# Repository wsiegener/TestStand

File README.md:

# Model Rocket Thrust Measurement Test Stand
* An RIT SPEX solo project developed by Billy Siegener

### Current Functionality
* Records and displays measurements from a 50kg load cell via an [HX711](https://cdn.sparkfun.com/datasheets/Sensors/ForceFlex/hx711_english.pdf "Amplifier datasheet") load cell amplifier module.
  * [HX711 Library](https://github.com/bogde/HX711 "HX711Library")
* Automatic scale factor tuning
* Improved tare functionality for dealing with noisy circuitry
* 1602A LCD implemenation

### Future Functionality
* ...

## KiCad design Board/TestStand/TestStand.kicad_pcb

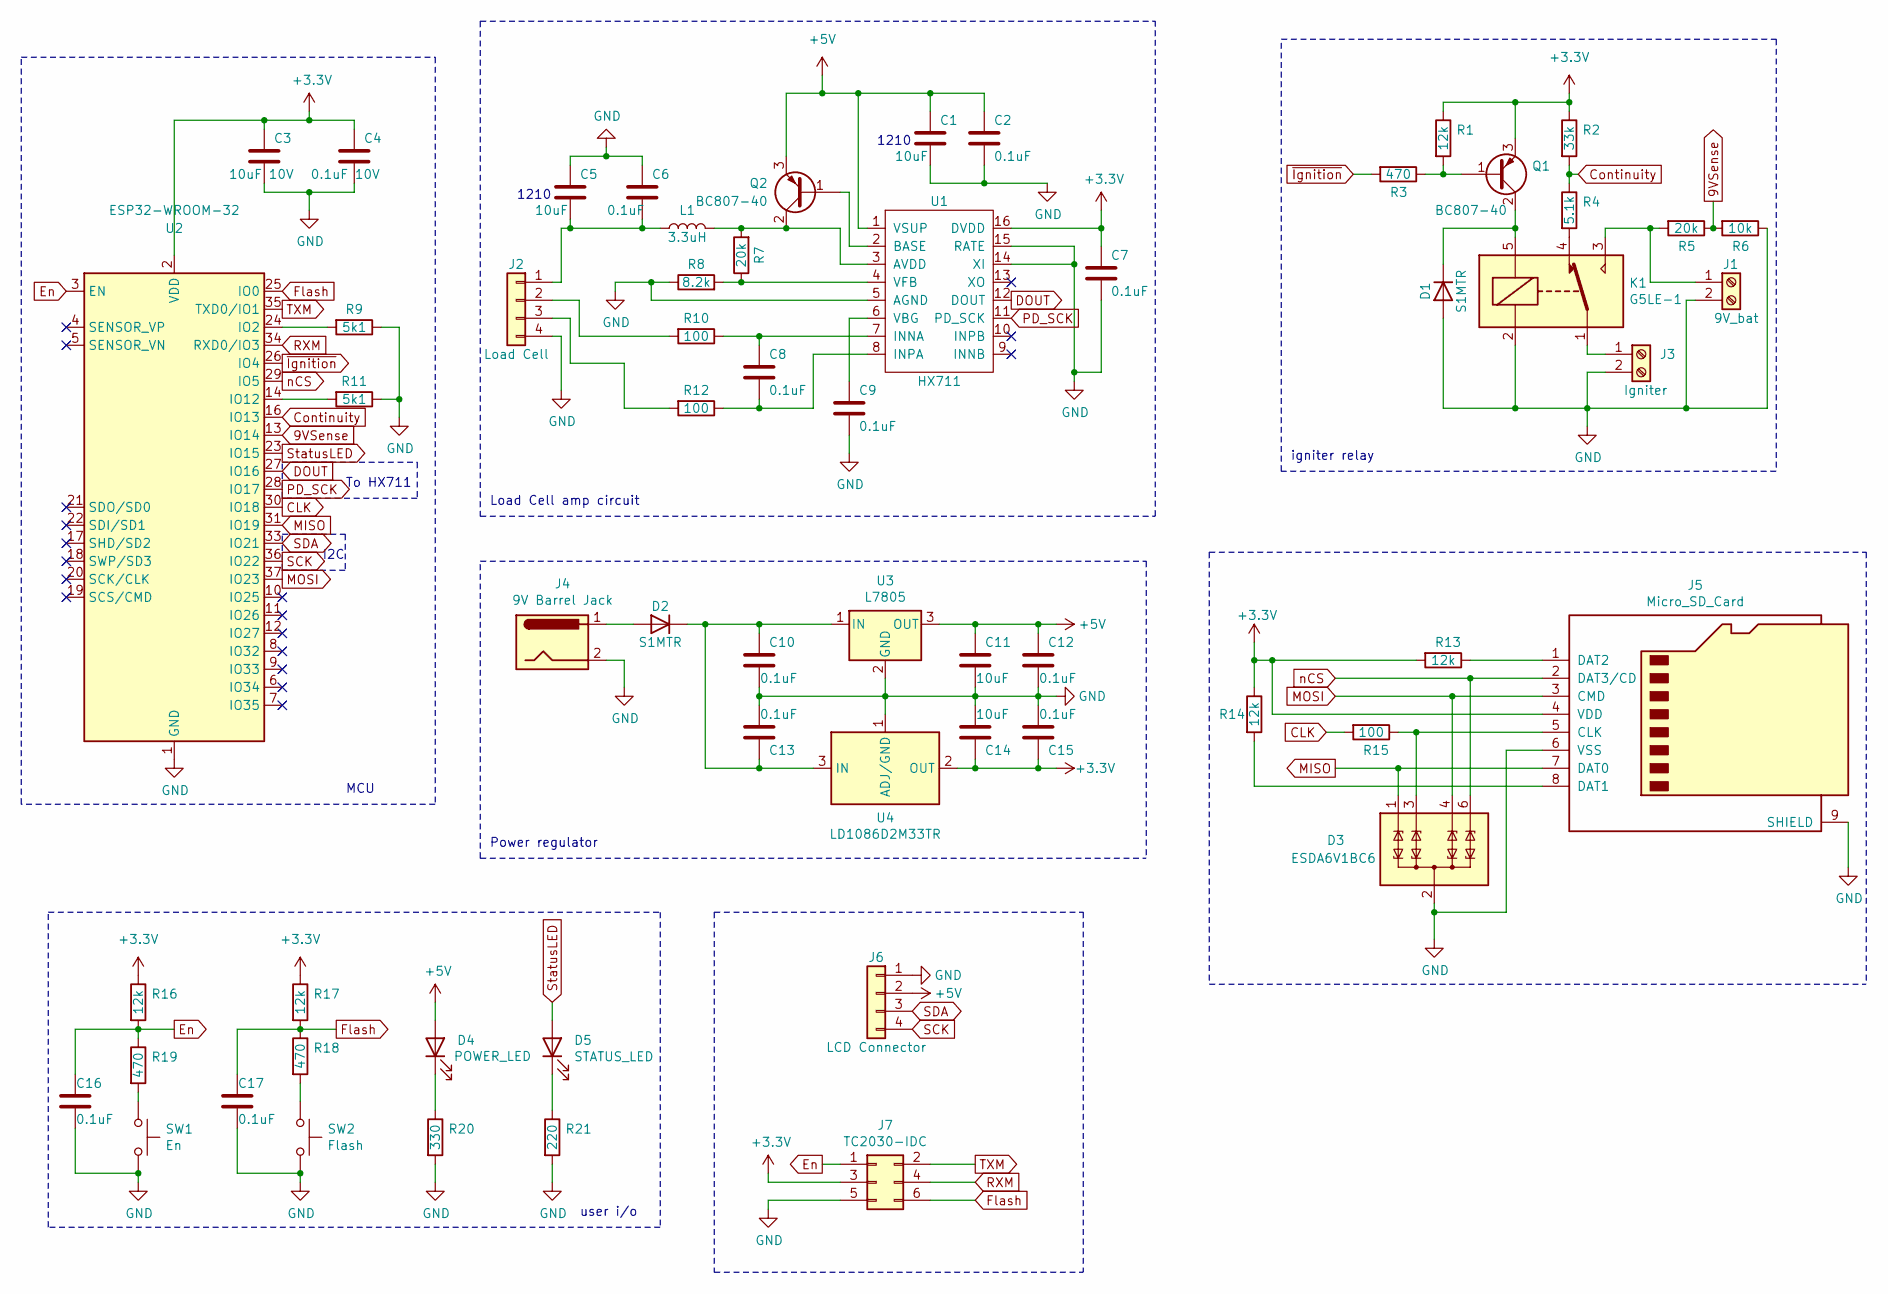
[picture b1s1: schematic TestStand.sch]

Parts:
C1, C5: 10uF; C_1210_3225Metric_Pad1.42x2.65mm_HandSolder
C2, C6, C7, C8, C9, C10, C12, C13, C15, C16, C17: 0.1uF; C_0805_2012Metric_Pad1.15x1.40mm_HandSolder
C3: 10uF 10V; C_0805_2012Metric_Pad1.15x1.40mm_HandSolder
C4: 0.1uF 10V; C_0805_2012Metric_Pad1.15x1.40mm_HandSolder
C11, C14: 10uF; C_0805_2012Metric_Pad1.15x1.40mm_HandSolder
D1, D2: S1MTR; D_SMA_Handsoldering
D3: ESDA6V1BC6; SOT-23-6
D4: POWER_LED; LED_Rectangular_W5.0mm_H2.0mm
D5: STATUS_LED; LED_Rectangular_W5.0mm_H2.0mm
J1: 9V_bat; TerminalBlock_Phoenix_PT-1,5-2-5.0-H_1x02_P5.00mm_Horizontal
J2: Load Cell; Molex_Micro-Fit_3.0_43045-0400_2x02_P3.00mm_Horizontal
J3: Igniter; TerminalBlock_Phoenix_PT-1,5-2-5.0-H_1x02_P5.00mm_Horizontal
J4: 9V Barrel Jack; BarrelJack_CUI_PJ-036AH-SMT_Horizontal
J5: Micro_SD_Card; microSD_HC_Molex_104031-0811
J6: LCD Connector; PinHeader_1x04_P2.54mm_Vertical
J7: TC2030-IDC; Tag-Connect_TC2030-IDC-FP_2x03_P1.27mm_Vertical
K1: G5LE-1; Relay_SPDT_Omron-G5LE-1
L1: 3.3uH; L_0805_2012Metric_Pad1.15x1.40mm_HandSolder
Q1, Q2: BC807-40; SOT-23_Handsoldering
R1, R13, R14, R16, R17: 12k; R_0805_2012Metric_Pad1.15x1.40mm_HandSolder
R2: 33k; R_0805_2012Metric_Pad1.15x1.40mm_HandSolder
R3, R18, R19: 470; R_0805_2012Metric_Pad1.15x1.40mm_HandSolder
R4: 5.1k; R_0805_2012Metric_Pad1.15x1.40mm_HandSolder
R5, R7: 20k; R_0805_2012Metric_Pad1.15x1.40mm_HandSolder
R6: 10k; R_0805_2012Metric_Pad1.15x1.40mm_HandSolder
R8: 8.2k; R_0805_2012Metric_Pad1.15x1.40mm_HandSolder
R9, R11: 5k1; R_0805_2012Metric_Pad1.15x1.40mm_HandSolder
R10, R12, R15: 100; R_0805_2012Metric_Pad1.15x1.40mm_HandSolder
R20: 330; R_0805_2012Metric_Pad1.15x1.40mm_HandSolder
R21: 220; R_0805_2012Metric_Pad1.15x1.40mm_HandSolder
SW1: En; SW_Push_1P1T_NO_6x6mm_H9.5mm
SW2: Flash; SW_Push_1P1T_NO_6x6mm_H9.5mm
U1: HX711; STC_SOP-16_3.9x9.9mm_P1.27mm
U2: ESP32-WROOM-32; ESP32-WROOM-32U
U3: L7805; TO-263-2
U4: LD1086D2M33TR; TO-263-3_TabPin2

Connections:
9VSense: R5.1, R6.2, U2.13 (IO14)
+3V3: C3.1, C4.1, C7.1, C14.2, C15.2, J5.4 (VDD), J7.3, Q1.3 (E), R1.1, R2.1, R13.2, R14.1, R16.1, R17.1, U1.16 (DVDD), U2.2 (VDD), U4.2 (OUT)
+5V: C1.1, C2.1, C11.1, C12.1, D4.2 (A), J6.2, Q2.3 (E), U1.1 (VSUP), U3.3 (OUT)
CLK: R15.2, U2.30 (IO18)
Continuity: R2.2, R4.1, U2.16 (IO13)
DOUT: U1.12 (DOUT), U2.27 (IO16)
En: C16.1, J7.1, R16.2, R19.1, U2.3 (EN)
Flash: C17.1, J7.6, R17.2, R18.1, U2.25 (IO0)
GND: C1.2, C2.2, C3.2, C4.2, C5.1, C6.1, C7.2, C9.2, C10.2, C11.2, C12.2, C13.1, C14.1, C15.1, C16.2, C17.2, D1.2 (A), D3.2 (COM), D3.5 (COM), J1.2, J2.4, J3.2, J4.2, J5.6 (VSS), J5.9 (SHIELD), J6.1, J7.5, K1.2, R6.1, R8.1, R9.1, R11.1, R20.2, R21.2, SW1.2, SW2.2, U1.5 (AGND), U1.14 (XI), U1.15 (RATE), U2.1 (GND), U2.15 (GND), U2.38 (GND), U2.39 (GND), U3.2 (GND), U4.1 (ADJ/GND)
Ignition: R3.2, U2.26 (IO4)
MISO: D3.1 (TVS1), J5.7 (DAT0), U2.31 (IO19)
MOSI: D3.4 (TVS3), J5.3 (CMD), U2.37 (IO23)
unnamed: C5.2, C6.2, J2.1, L1.1
unnamed: C8.1, R10.1, U1.7 (INNA)
unnamed: C8.2, R12.1, U1.8 (INPA)
unnamed: C9.1, U1.6 (VBG)
unnamed: C10.1, C13.2, D2.1 (K), U3.1 (IN), U4.3 (IN)
unnamed: D1.1 (K), K1.5, Q1.2 (C)
unnamed: D2.2 (A), J4.1
unnamed: D3.3 (TVS2), J5.5 (CLK), R15.1
unnamed: D4.1 (K), R20.1
unnamed: D5.1 (K), R21.1
unnamed: J1.1, K1.3, R5.2
unnamed: J2.2, R10.2
unnamed: J2.3, R12.2
unnamed: J3.1, K1.1
unnamed: J5.1 (DAT2), R13.1
unnamed: J5.8 (DAT1), R14.2
unnamed: K1.4, R4.2
unnamed: L1.2, Q2.2 (C), R7.2, U1.3 (AVDD)
unnamed: Q1.1 (B), R1.2, R3.1
unnamed: Q2.1 (B), U1.2 (BASE)
unnamed: R7.1, R8.2, U1.4 (VFB)
unnamed: R9.2, U2.24 (IO2)
unnamed: R11.2, U2.14 (IO12)
unnamed: R18.2, SW2.1
unnamed: R19.2, SW1.1
PD_SCK: U1.11 (PD_SCK), U2.28 (IO17)
RXM: J7.4, U2.34 (RXD0/IO3)
SCK: J6.4, U2.36 (IO22)
SDA: J6.3, U2.33 (IO21)
StatusLED: D5.2 (A), U2.23 (IO15)
TXM: J7.2, U2.35 (TXD0/IO1)
nCS: D3.6 (TVS4), J5.2 (DAT3/CD), U2.29 (IO5)

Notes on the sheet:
I2C
1210
Load Cell amp circuit
Power regulator
user i/o
MCU
To HX711
igniter relay

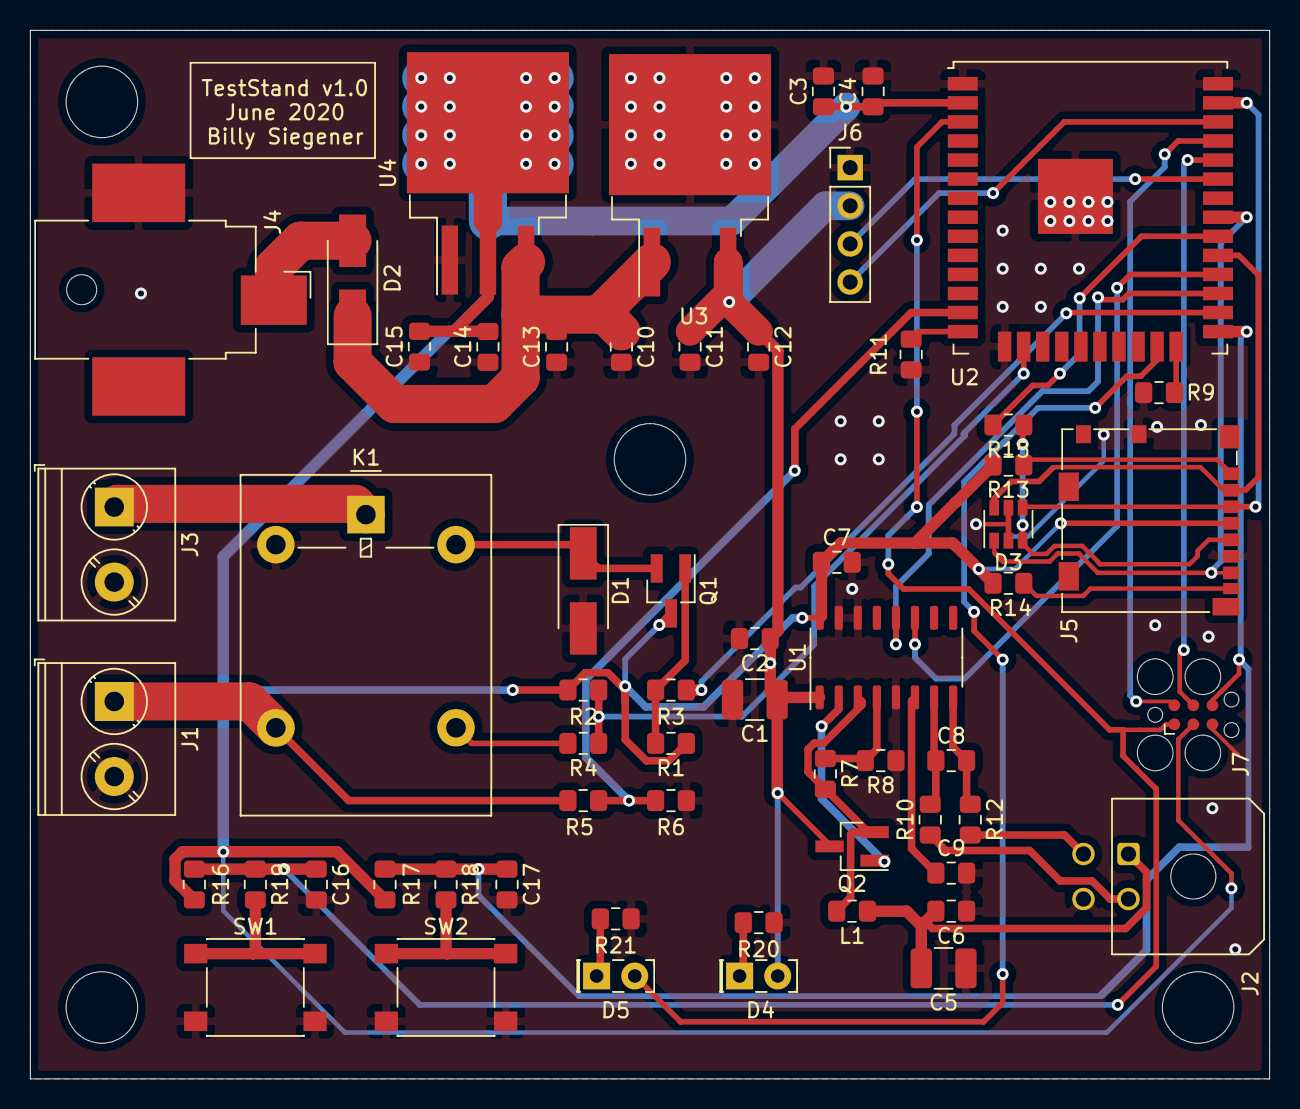
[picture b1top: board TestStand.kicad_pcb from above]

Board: 2 copper layers, 82.5 x 69.9 mm, 60 parts (0 on the bottom side), 44 nets.

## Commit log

2020-02-13 Initial commit: - Working readings from loadcell - Scale factor tuning - Improved tare functionality
2020-02-13 - fix project settings
2020-02-14 - add basic transmitter code
2020-05-28 - refactor file heirarchy - add wireless testing code
2020-05-28 - more refactoring
2020-07-01 - add kicad board schematic and pcb design - add state machine logic
